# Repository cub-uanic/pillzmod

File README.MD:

# Pillz Mod for the Kinesis Advantage/Contoured

This project replaces my two previous forks ([kinesismod](https://github.com/dcpedit/kinesismod) and [kint](https://github.com/dcpedit/kint)) for adding Blackpill support to the Kinesis keyboard.  I've decided to merge all the features into a single PCB, add optional thumb cluster PCBs as part of the kit, and renamed the project to avoid confusion.  Below is a list of supported features.

* Supports Blackpill development board running QMK/Vial
* Supports Pill Bug wireless Bluetooth development board running ZMK
* Optional reversible thumb cluster PCB for left/right sides.  (Maintains original matrix wiring)
* 2u stabilizer support on thumb cluster

## "Pro" PCB Features

* Supports devlopment board with Pro-Micro footprint (Elite-C, Elite-Pi, Nice!Nano)
* Header for connecting up to 3 foot-pedals
* Piezo audio buzzer
* Header for extra data pin (Elite-C only)

## Attribution

Credit goes to the following people for doing all the initial development on replacment PCBs for the Kinesis:
 * Aaron Silman's [kinesismod project](https://gitlab.com/Silman/kinesismod.git) ([blog](https://silman.io/project/kinesis_mod/))
 * Michael Stapelberg's [KinT project](https://github.com/kinx-project/kint) ([blog](https://michael.stapelberg.ch/posts/2020-07-09-kint-kinesis-keyboard-controller/))
 * Dmitry Nosachev's [Kin80 project](https://github.com/DmNosachev/kin80)

## Ordering PCBs from JLCPCB

The files needed for https://jlcpcb.com are located in the production folders:
* Choose `pcb-pro/production`, `pcb-pro-nrf/production` or `pcb/production` 
* `thumb-pcb/production`

Once uploaded, you place the order with the selected default options.  You can optionally change the solder mask color, which changes the final color of your PCB.

## Main PCB build guide
### Components
| Position | Description | Qty | Notes |
| -------- | ----------- | --- | ----- |
| J1-J4    | Molex 39-53-2135 | 2 - 6  | [Link](https://octopart.com/39-53-2135-molex-7670149?r=sp)
| J3-J4    | Molex 39-53-2134 | 0 - 2  | Contoured only, [Link](https://octopart.com/search?q=Molex+39-53-2134)
| U1       | Header pins (1x20) | 2 | Should come with dev board
| U1       | Headers (1x20) | 2 | To socket your dev board
| D1-D4    | 1.8mm LED | 4 | [Amazon](https://a.co/d/90uynIs)
| R1-R4    | 10k resistor | 4 | Affects LED brightness. Smaller = brighter |
|          | USB-C panel mount | 1 | [AliExpress](https://www.aliexpress.us/item/3256806463941289.html?spm=a2g0o.order_list.order_list_main.43.18a31802pDYB6d&gatewayAdapt=glo2usa), [Amazon](https://a.co/d/cRoqHqx)

### Blackpill Components
| Position | Description | Qty | Notes |
| -------- | ----------- | --- | ----- |
| U1       | Blackpill (STM32F411) | 1 | [WeAct Store](https://www.aliexpress.com/store/1101545918?spm=a2g0o.order_list.order_list_main.2.18a31802pDYB6d)

#### -or- Pill Bug for wireless build

| Description | Qty | Notes |
| ----------- | --- | ----- |
| Pill Bug | 1 | [MechWild Store](https://mechwild.com/product/pillbug/)
| 3.7V battery | 1 | [2000mAh](https://a.co/d/dVUdHxi)
| Power button | 1 | Optional, [10mm](https://a.co/d/i33uBM0) or [19mm](https://a.co/d/fYN6ZX5)

### Additional "Pro" Components

| Position | Description | Qty | Notes |
| -------- | ----------- | --- | ----- |
| U1       | Elite-C/Elite-Pi | 1 |
|          | 3.7V battery | 1 | [2000mAh](https://a.co/d/dVUdHxi)
| U2       | 74HC595      | 1 | [Amazon](https://a.co/d/eLX9kOY)
| U2       | 16-pin IC socket | 1 | [Amazon](https://a.co/d/5EaFAHo)
| D6-D8    | 1n4148 Diode | 3 | [Link](https://www.mouser.com/ProductDetail/512-1N4148TR)
| BZ1      | Piezo Buzzer | 1 | [Link](https://www.digikey.com/en/products/detail/tdk-corporation/PS1240P02BT/935924)
| SW1      | Reset button | 1 | [Link](https://www2.mouser.com/ProductDetail/Alps-Alpine/SKQGAEE010?qs=N5Jky1br14PyTRvcw7F3eQ%3D%3D)
| R5-R19   | 10k Resistor | 15| AVR/Elite-C Only [Link](https://www.mouser.com/ProductDetail/YAGEO/MFR-12FTF52-10K?qs=oAGoVhmvjhzLlUYKKBtdYQ%3D%3D), [Link](https://mou.sr/3xgqcNf)

#### -or- Nice!Nano for wireless build

| Description | Qty | Notes |
| ----------- | --- | ----- |
| Nice!Nano    | 1 | [Website](https://nicekeyboards.com/nice-nano/)
| 3.7V battery | 1 | [2000mAh](https://a.co/d/dVUdHxi)
| Power button | 1 | Optional, [10mm](https://a.co/d/i33uBM0) or [19mm](https://a.co/d/fYN6ZX5)

### Instructions

_NOTE: If you're using a battery that's larger than 500mAh, then bridge the charge boost jumper labeled JP1 with some solder.  This will increases the max charge rate from 100mA to 500mA. Doing this for small batteries (<500mAh) may cause explosions._

All components go on the side with the silkscreen labels (rectangles) EXCEPT for the LEDs.  First solder the header pins onto your development board, and the header sockets onto the PCB.  I prefer to use Mill-Max 310 series sockets because the pins are thin.  Then solder in the LED resistors, but NOT the actual LEDs yet.  The resistors can be SMD or through hole.

For a wireless build, you can now solder the battery wires/connector to the board.  Make sure the positive wire goes into "BAT+", and the negative wire goes into "BAT-".  If you're using a power button, make sure to wire it inline along the BAT+ wire so that it essentially opens and closes the circuit.

Insert your development board into the sockets on the PCB.

For the Molex connectors, I find that it's more convient to desolder the ones on the original PCB so that I don't have to purchase new ones.  Solder the connectors onto the PCB.

Flip the PCB over and insert the LEDs on the side of the PCB with no other components.  Make sure the short leg goes into the square pad, and bend the legs so that they stay in place.  Screw the PCB back into the keyboard case, making sure the LEDs are lined up with the existing case holes.  You can also adjust the height of the LED to move them closer to the status window if you'd like.  Once you're satisfied with the position of the LEDs, you can then solder them in place while the PCB is still mounted.

Lastly, plug the USB-C panel mount cable to into the development board, and secure the other end to the hole in the case.

### "Pro" Additional Instructions

The components required for this build and their position will depend on the development board you're using.  For example, pull-down resistors R5-R19 are only needed for AVR chips (Pro-Micro, Elite-C) since they don't support internal pull-downs for the row inputs.  Use the image below as a guide.

The Elite-C has an extra B0 pin that is broken out into the J10 pins.  You can use this to drive other components if you choose (ie. RGB strip, Solenoid)

* Pin 1 (square pad) - VCC
* Pin 2 - B0
* Pin 3 - GND

The J9 pins are for foot pedals and have the following assignment:

* Pin 1 (square pad) - Col6
* Pin 2 - Row0
* Pin 3 - Row1
* Pin 4 - Row2

Diodes D6-D8 are connected to the rows, so no additional diodes are needed in the pedals/switches.

### "Pro" Nice!Nano Additional Instructions

Mill-Max 310 sockets are recommended for socketing the Nice!Nano because thin pins are required for connecting the extra 3 pins in the middle.

The Nice!Nano is one pin short of supporting all 4 status lights on the Advantage.  If you want to utilize the unused numpad status LED as a power indicator, go ahead and short JP1 with some solder.

### SuperMini NRF52840

For [SuperMini NRF52840](https://github.com/joric/nrfmicro/wiki/Alternatives), use `pcb-pro-nrf` - it has 3 additional holes at correct place.

## Thumb cluster PCB build guide

The wiring for the thumb cluster (a.k.a. matrix wiring) has not been altered from original, so theoretically, they can be used in conjunction with any Kinesis PCB, including the stock one.

The PCB is also reversible, so you don't have to place separate orders for a "left" version and a "right" version.

### Components

| Description | Qty | Notes |
| ----------- | --- | ----- |
| 1N4148 SOD-123 diode | 12 | [Amazon](https://a.co/d/gsv8bGT)
| MX switch | 12 | Can desolder and reuse
| 2u screw-in stabilizer | 4 | [Link](https://divinikey.com/products/durock-v2-stabilizers-screw-in)
| Cable connector (1x10) | 4 | 2.54mm pitch (eg KF2510)
| Ribbon cable | 2 | >= 50mm length

### Instructions

You will need two PCBs for the thumb cluster, but since they're reversible, you will need to read the silkscreen to see if it's the left or right cluster.

First step is to solder all the 1N4148 diodes.  Orientation matters, so make sure the line on the diode faces same direction as the thicker white line on the PCB.  Place a dab of solder on ONE of the two diode pads.  Drop the diode into position (double checking the orientation), hold the diode in place with tweezers, and melt the solder you just added to the pad so that diode is held in place.  Now add solder to the opposite pad, thus holding the other diode leg in place.  Repeat for all the other diodes.

The connector for the ribbon cable can now be soldered onto the PCB, and will be on the same side as the diodes.  The pin pitch is 2.54mm, so any compatible connector/cable will work here.

Install the 2u stabilizers onto the PCB.

Now solder in your MX switches.  If you're reusing the original switches, desolder them from the original PCB, and remove the diode from inside the switch housing.  Using a switch opener will make this task much easier.

Mount the thumb clusters onto the keyboard and connect the ribbon cables.

## QMK firmware for "Pro"

* `firmware/pro_qmk_avr_default.bin`
* `firmware/pro_qmk_rp2040_default.uf2`

QMK source: https://github.com/dcpedit/qmk_firmware/tree/pillzmod/keyboards/dcpedit/pillzmod

## Vial firmware for Blackpill

* `firmware/blackpill_vial.bin`
* `firmware/dcpedit_kint_bp_vial_6layers.bin`

Source: https://github.com/dcpedit/vial-qmk/tree/pillzmod/keyboards/dcpedit/pillzmod

Remap keys: https://vial.rocks/

### Flashing firmware under Linux
The file firmware/dcpedit_kint_bp_vial_6layers.bin (or other) can simply be flashed to the Blackpill using the dfu-util. The dfu-util tool requires root privileges if settings are not accessible by the user.

Connect Blackpill to your Linux PC via USB C cable and start unit in DFU mode by holding bootp button and pressing reset button. Wait a second and release the bootp button.

Check the DFU devices by running
```
dfu-util -l
```
The Blackpill device should be visible.

Write the firmware to the device with
```
dfu-util -d 0483:df11 -a 0 -s 0x08000000 -D [PATH TO kint]/firmware/dcpedit_kint_bp_vial_6layers.bin
```

## Vial firmware for "Pro"

* `firmware/pro_vial_avr.hex`

Source: https://github.com/dcpedit/vial-qmk/tree/pillzmod/keyboards/dcpedit/pillzmod
(You will need to clone the entire branch since I had to make a core code change in `spi_master.c`)

## ZMK firmware for Pill Bug

* `firmware/zmk_default.uf2` - Default keymap
* `firmware/zmk_custom.uf2` - Support for up to 6 layers
* `firmware/zmk_reset.uf2` - Resets PillBug board for BT connectivity issue on MacOS      
* `firmware/zmk_studio.uf2` - Studio compatible (Progrm + Esc to unlock)

Source: https://github.com/dcpedit/zmk/tree/pillzmod/app/boards/shields/pillzmod

### Bluetooth with ZMK

The ZMK firmware has mappings for performing system tasks. By default there are 4 Bluetooth pairings saved to the keyboard but they do not switch automatically when adding new devices. So after you add the first device, you need to tell they keyboard to use Bluetooth slot 2 and so forth.
The keys to switch between are accessed by a different keyboard layer. This layer is opened by holding down the "Program" key at the very top right of the Kinesis and, while holding it, then clicking another key as follows:

* **Clear all saved Bluetooth profiles:** Program + F9
* **Bluetooth profile 1:** Program + F1
* **Bluetooth profile 2:** Program + F2
* **Bluetooth profile 3:** Program + F3
* **Bluetooth profile 4:** Program + F4
* **Enter bootloader mode (to upload UF2 files):** Program + - (the dash key just below program)

If you want to do a ZMK firmware build using GitHub actions, take a look at the following repository from keepitsimplejim:

https://github.com/keepitsimplejim/zmk-config-pillzmod-kinesis-adv

## ZMK firmware for "Pro" Nice!Nano

* `firmware/pro_zmk.uf2` - Default keymap
* `firmware/pro_zmk_studio.uf2` - Studio compatible (Progrm + Esc to unlock)

Source: https://github.com/dcpedit/zmk/tree/pillzmod/app/boards/shields/pillzmod_pro
Studio: https://zmk.studio/

## KiCad

All the PCBs were designed using KiCad, which is free and can be downloaded here: https://www.kicad.org/

For the thumb cluster PCB, I wasn't able to figure out how to have the left and right wiring co-exist without errors while sharing the same connector footprint.  My workaround was to first change the connector's reference designator to "J1", update the PCB from schematic, and wire up the left side.  Then I changed the reference designator to "J2", updated the PCB from schematic again, and wired up the right side.

If there are any KiCad experts out there that know of a more elegant solution, please let me know.

The production JLCPCB files are all generated with Fabrication Toolkit: https://github.com/bennymeg/Fabrication-Toolkit

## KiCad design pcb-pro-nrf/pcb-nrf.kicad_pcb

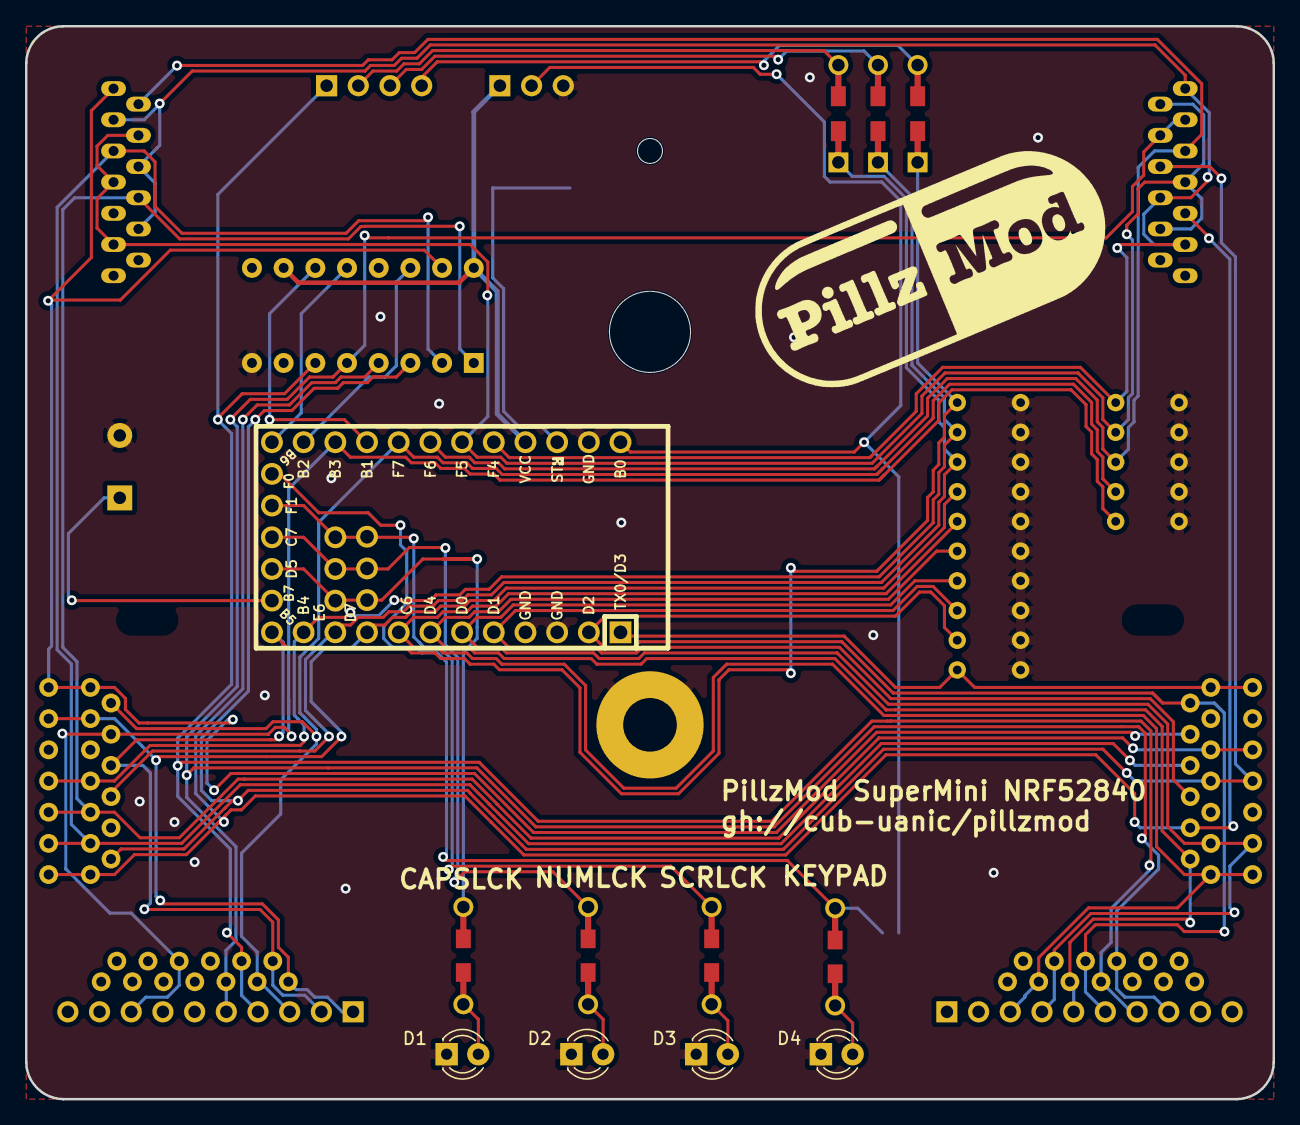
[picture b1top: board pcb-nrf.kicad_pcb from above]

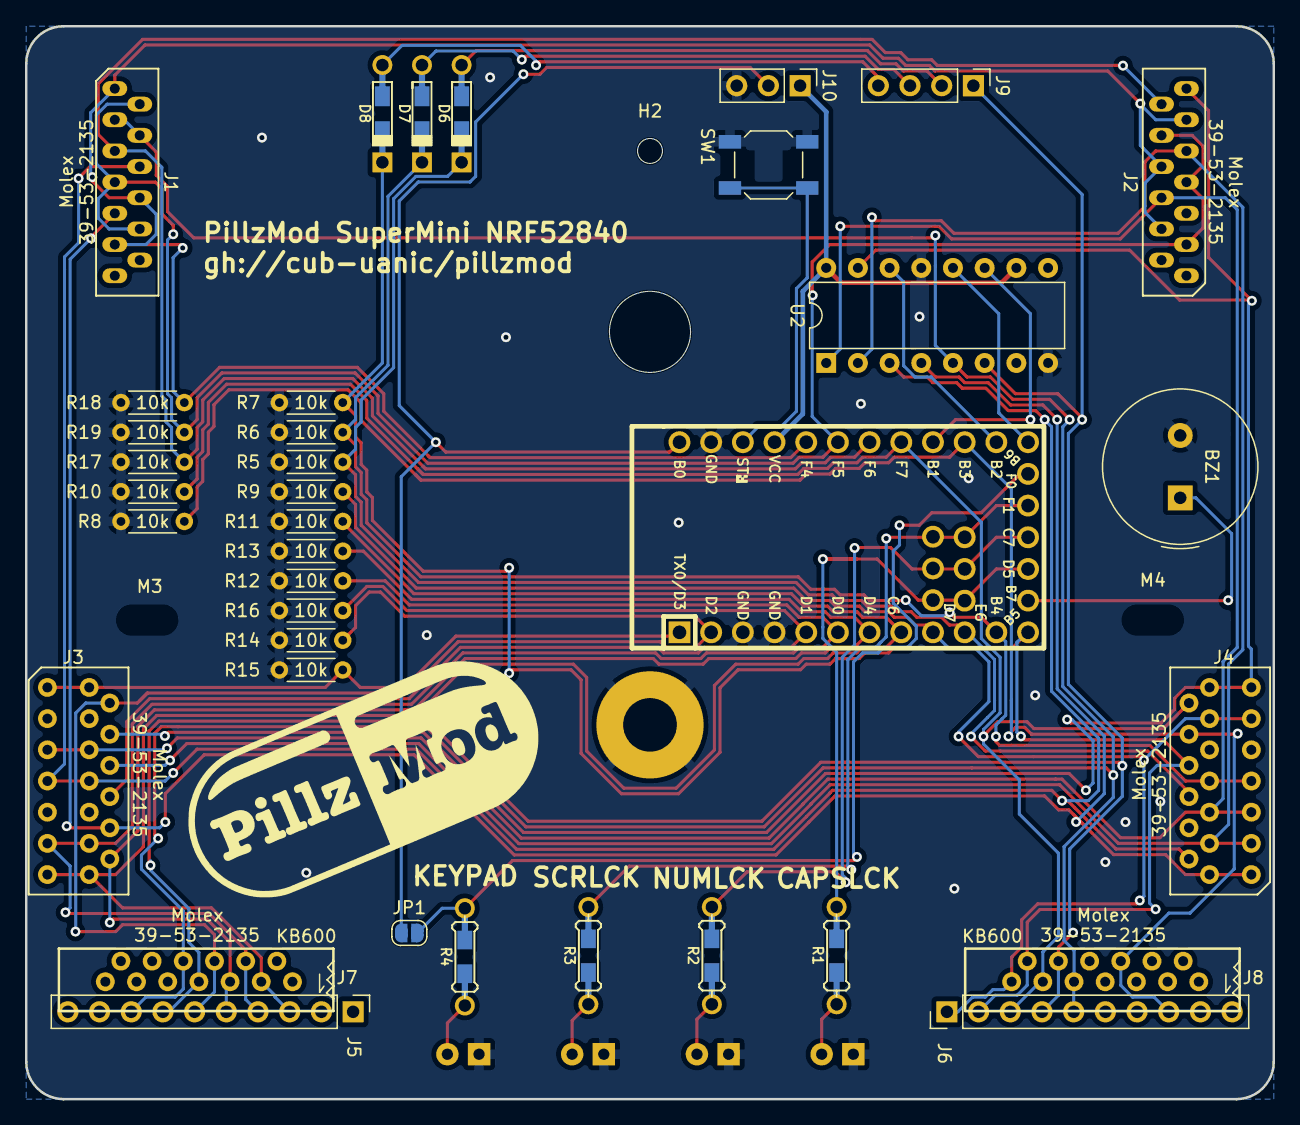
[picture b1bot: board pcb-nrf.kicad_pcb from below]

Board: 2 copper layers, 100.0 x 86.0 mm, 46 parts (41 on the bottom side), 41 nets.

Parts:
BZ1: Buzzer; Buzzer_TDK_PS1240P02BT_D12.2mm_H6.5mm
D1: LED_CAPS; LED_D3.0mm
D2: LED_NUM; LED_D3.0mm
D3: LED_SCR; LED_D3.0mm
D4: LED_ALT; LED_D3.0mm
D6, D7, D8: D_Small; Diode-dual
H1: mounting pad; MountingHole_4.3mm_M4_Pad
H2: mounting pad; MountingHole_2mm
J1, J2: Conn_01x13; Molex_0039532135
J3, J4: Conn_01x13; Molex_039532134
J5, J6: Conn_01x10; Pin_Header_Straight_1x10_Pitch2.54mm
J7, J8: Conn_01x13; 39-53-2135
J9: Conn_01x04; PinHeader_1x04_P2.54mm_Vertical
J10: Extra; PinHeader_1x03_P2.54mm_Vertical
JP1: SolderJumper_2_Open; SolderJumper-2_P1.3mm_Open_RoundedPad1.0x1.5mm
M1: MountingHole_6.4mm_M6
M3, M4: MountingHole_4.3mm_M4
R1, R2, R3, R4: R_US; Resistor-Hybrid
R5, R6, R7, R8, R9, R10, R11, R12, R13, R14, R15, R16, R17, R18, R19: 10k; R_Axial_DIN0204_L3.6mm_D1.6mm_P5.08mm_Horizontal
SW1: RESET; SW_SPST_SKQG_WithoutStem
U1: Elite-C
U2: 74HC595; DIP-16_W7.62mm

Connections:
+5V: J10.1, U1.21 (VCC), U2.10 (~SRCLR), U2.16 (VCC)
/BUZ: BZ1.1 (-), U1.25 (B7)
/COL_0: J2.13, J3.4, J4.13, U2.15 (QA)
/COL_1: J2.6, J3.5, J4.5, U2.1 (QB)
/COL_2: J2.9, J3.6, J4.3, U2.2 (QC)
/COL_3: J1.6, J3.7, J4.2, U2.3 (QD)
/COL_4: J1.9, J3.10, J4.1, U2.4 (QE)
/COL_5: J1.3, J1.4, J5.8, J6.5, J7.8, J8.9, U2.5 (QF)
/COL_6: J5.7, J6.4, J7.7, J8.10, J9.1, U2.6 (QG)
/EXTRA: J10.2, JP1.1 (A), U1.24 (B0)
/LATCH: U1.13 (10/PB6), U2.12 (RCLK)
/LED_CAPS_LOCK: R1.2, U1.26 (D5)
/LED_KEYPAD: JP1.2 (B), R4.2, U1.29 (F0)
/LED_NUM_LOCK: R2.2, U1.27 (C7)
/LED_SCROLL_LOCK: R3.2, U1.28 (F1)
/RESET: SW1.1 (A), U1.22 (RST)
/ROW_0: D6.1 (K), J4.6, R5.1, U1.10 (7/PE6)
/ROW_1: D7.1 (K), J4.7, R6.1, U1.11 (8/PB4)
/ROW_2: D8.1 (K), J4.8, J6.2, J8.12, R7.1, U1.12 (9/PB5)
/ROW_3: J4.10, J6.8, J8.6, R8.1, U1.15 (14/PB3)
/ROW_4: J4.11, J6.1, J8.13, R9.1, U1.9 (6/PD7)
/ROW_5: J4.12, J6.3, J8.11, R10.1, U1.17 (A0/PF7)
/ROW_6: J3.13, J5.3, J7.3, R11.1, U1.8 (5/PC6)
/ROW_7: J3.11, J5.4, J7.4, R12.1, U1.6 (3/PD0)
/ROW_8: J3.12, J5.5, J7.5, R13.1, U1.7 (4/PD4)
/ROW_9: J3.2, J5.6, J7.6, R14.1, U1.2 (RX1/PD2)
/ROW_10: J3.1, R15.1, U1.1 (TX0/PD3)
/ROW_11: J3.8, R16.1, U1.5 (2/PD1)
/ROW_12: J1.5, J2.12, R17.1, U1.18 (A1/PF6)
/ROW_13: J1.1, J1.8, J1.11, J2.4, J2.8, J2.11, R18.1, U1.20 (A3/PF4)
/ROW_14: J1.2, J1.7, J1.10, J2.3, J2.7, J2.10, R19.1, U1.19 (A2/PF5)
/SPI_MOSI: U1.14 (16/PB2), U2.14 (SER)
/SPI_SCK: U1.16 (15/PB1), U2.11 (SRCLK)
GND: BZ1.2 (+), D1.1 (K), D2.1 (K), D3.1 (K), D4.1 (K), H1.1, J10.3, R5.2, R6.2, R7.2, R8.2, R9.2, R10.2, R11.2, R12.2, R13.2, R14.2, R15.2, R16.2, R17.2, R18.2, R19.2, SW1.2 (B), U1.3 (GND), U1.4 (GND), U1.23 (GND), U2.8 (GND), U2.13 (~OE)
unnamed: D1.2 (A), R1.1
unnamed: D2.2 (A), R2.1
unnamed: D3.2 (A), R3.1
unnamed: D4.2 (A), R4.1
unnamed: D6.2 (A), J9.2
unnamed: D7.2 (A), J9.3
unnamed: D8.2 (A), J9.4
